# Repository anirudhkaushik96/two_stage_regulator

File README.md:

# two_stage_regulator
Two stage DC Voltage Regulator

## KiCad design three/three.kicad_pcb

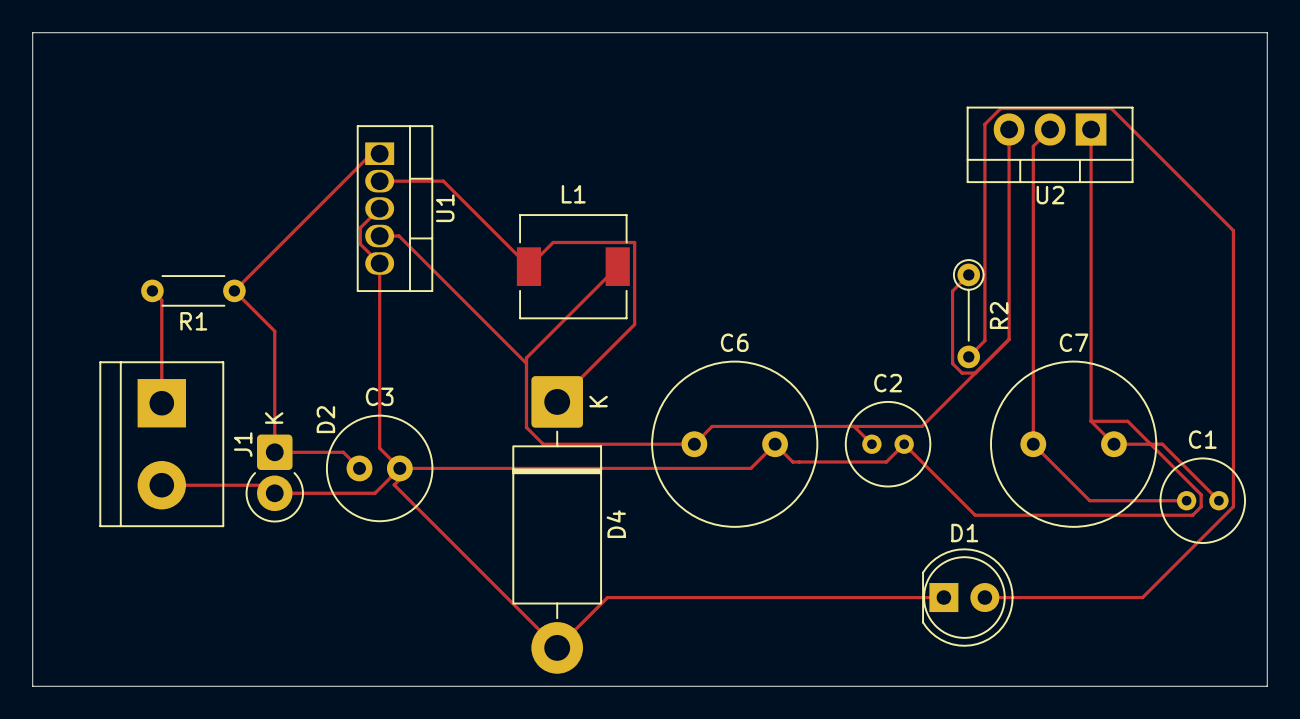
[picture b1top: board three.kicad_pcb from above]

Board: 2 copper layers, 76.5 x 40.5 mm, 14 parts (0 on the bottom side), 7 nets.

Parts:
C1, C2: C; C_Radial_D5.0mm_H5.0mm_P2.00mm
C3: c=100u; C_Radial_D6.3mm_H11.0mm_P2.50mm
C6, C7: c=1000u; C_Radial_D10.0mm_H12.5mm_P5.00mm
D1: LED; LED_D5.0mm
D2: D; D_DO-41_SOD81_P2.54mm_Vertical_KathodeUp
D4: 1N5822; D_DO-201AD_P15.24mm_Horizontal
J1: Screw_Terminal_01x02; TerminalBlock_bornier-2_P5.08mm
L1: l=100u; L_6.3x6.3_H3
R1: R; R_Axial_DIN0204_L3.6mm_D1.6mm_P5.08mm_Horizontal
R2: R; R_Axial_DIN0204_L3.6mm_D1.6mm_P5.08mm_Vertical
U1: LM2576T-5; TO-220-5_Vertical
U2: LD1117V; TO-220-3_Vertical

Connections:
GND: C1.2, C2.2, C3.2, C6.2, C7.2, D1.1 (K), D2.2 (A), D4.2 (A), J1.2, U1.3 (GND), U1.5 (~ON/OFF), U2.1 (GND)
unnamed: D1.2 (A), R2.2
unnamed: C3.1, D2.1 (K), R1.1, U1.1 (VIN)
unnamed: D4.1 (K), L1.1, U1.2 (OUT)
unnamed: J1.1, R1.2
unnamed: C2.1, C6.1, L1.2, R2.1, U1.4 (FB), U2.3 (VI)
unnamed: C1.1, C7.1, U2.2 (VO)

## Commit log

2025-08-21 KiCAD files for voltage regulator circuits
    Change the path of the .subckt files to the path where your .subckt files are saved.
